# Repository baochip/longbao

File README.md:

# Longbao

Design files for the Longbao full pin breakout for the Baochip-1x.

The design is split into two halves, a small HDI board that uses laser-drilled vias to break out all the pins,
and a large conventional board that simply fans the break-out to castellated holes for easy prototyping.

The intention is that users who do not want to fab out an HDI board could re-use the HDI board in their design
as a "SOM".

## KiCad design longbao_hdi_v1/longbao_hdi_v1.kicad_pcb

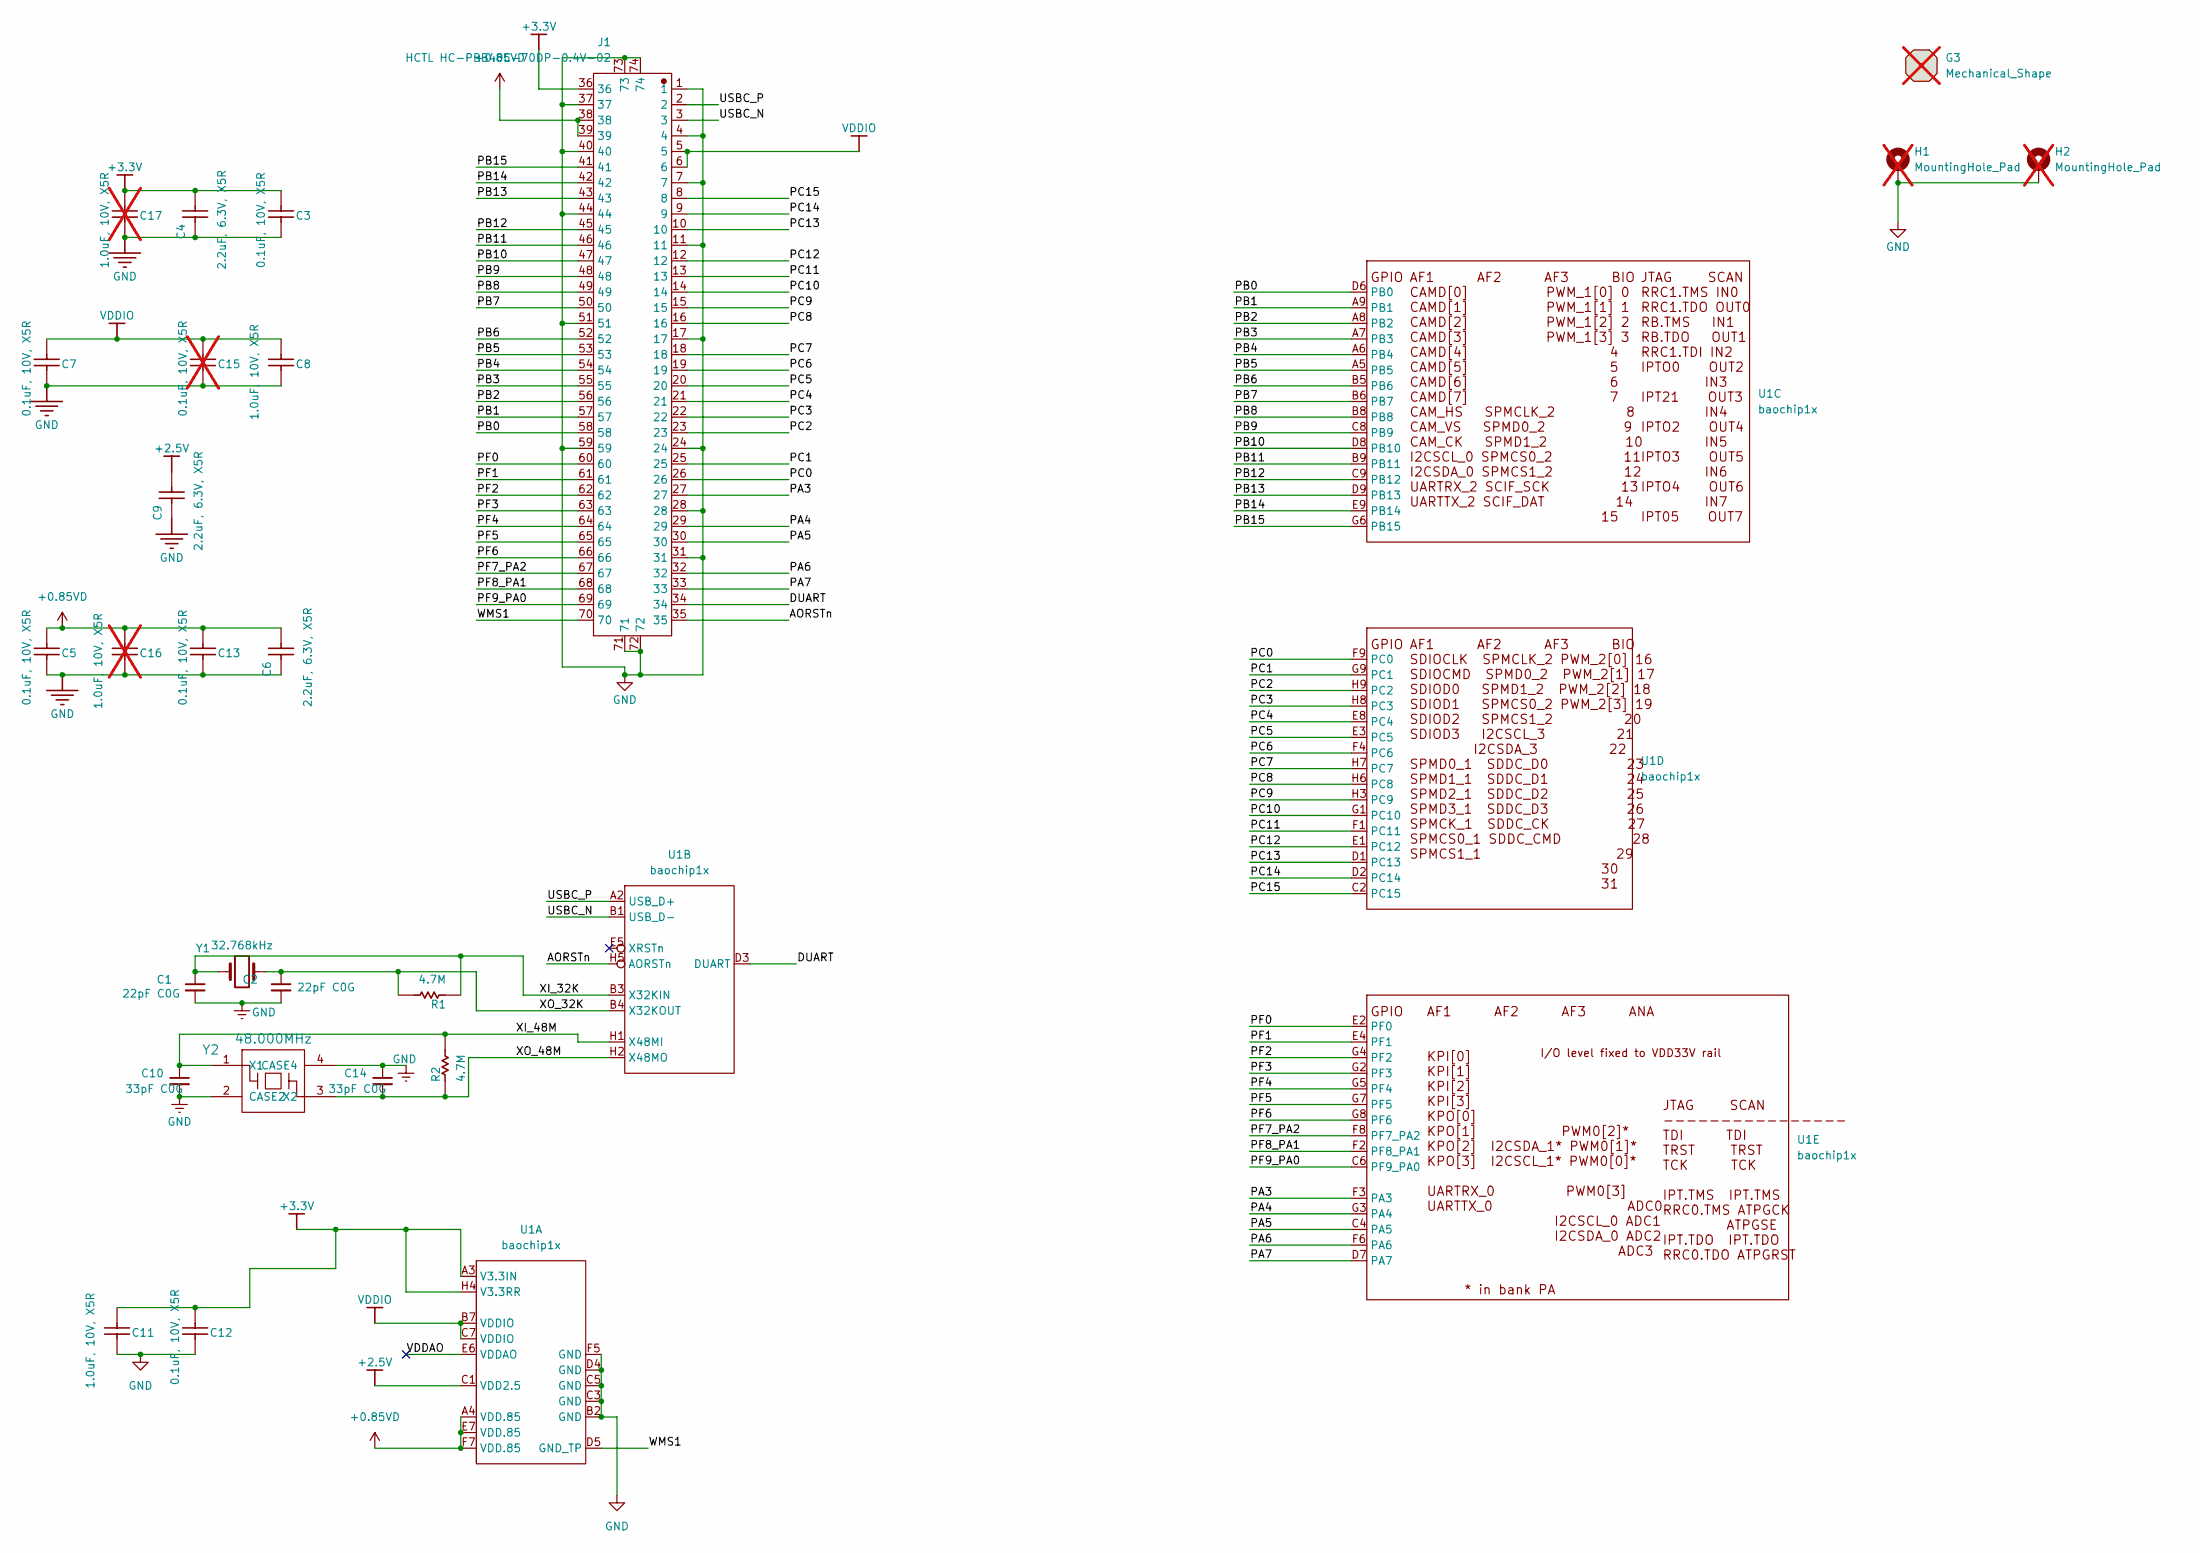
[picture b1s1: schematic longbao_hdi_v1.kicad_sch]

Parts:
C1, C2: 22pF C0G; C_0201_0603Metric; Rating C0G 50V 0201; MPN ANY; LCSC C57783
C3, C5, C7, C12, C13: 0.1uF, 10V, X5R; C_0201_0603Metric; MPN CL05B104KO5NNNC; LCSC C76934
C4, C6, C9: 2.2uF, 6.3V, X5R; C_0201_0603Metric; MPN GRM033R60J225ME47D; LCSC C76933
C8, C11: 1.0uF, 10V, X5R; C_0201_0603Metric; MPN CL05A105KA5NQNC; LCSC C76935
C10, C14: 33pF C0G; C_0201_0603Metric; Rating C0G 50V 0201; MPN ANY; LCSC C56903
C15: 0.1uF, 10V, X5R; C_0201_0603Metric; MPN CL05B104KO5NNNC; LCSC C76934; not fitted
C16, C17: 1.0uF, 10V, X5R; C_0201_0603Metric; MPN CL05A105KA5NQNC; LCSC C76935; not fitted
G3: Mechanical_Shape; CE-Logo_8.5x6mm_SilkScreen; not fitted
H1, H2: MountingHole_Pad; MountingHole_2.2mm_M2_DIN965_Pad; not fitted
J1: HCTL HC-PBB40C-70DP-0.4V-02; HC-PBB40C-70DP-0.4V-02; LCSC C19089236
R1, R2: 4.7M; R_0402_1005Metric; MPN ANY; LCSC C474132
U1: baochip1x; WLCSP-71_9x8_4.062x3.762mm; LCSC C9900312212
Y1: 32.768kHz; Crystal_SMD_TXC_9HT11-2Pin_2.0x1.2mm; LCSC C55208
Y2: 48.000MHz; Crystal_SMD_3225-4Pin_3.2x2.5mm; LCSC C2892060

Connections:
+0.85VD: C5.1, C6.2, C13.1, C16.1, J1.38, J1.39, U1.A4 (VDD.85), U1.E7 (VDD.85), U1.F7 (VDD.85)
+2.5V: C9.2, U1.C1 (VDD2.5)
+3.3V: C3.1, C4.2, C11.1, C12.1, C17.1, J1.36, U1.A3 (V3.3IN), U1.H4 (V3.3RR)
/AORSTn: J1.35, U1.H5 (AORSTn)
/DUART: J1.34, U1.D3 (DUART)
/PA3: J1.27, U1.F3 (PA3)
/PA4: J1.29, U1.G3 (PA4)
/PA5: J1.30, U1.C4 (PA5)
/PA6: J1.32, U1.F6 (PA6)
/PA7: J1.33, U1.D7 (PA7)
/PB0: J1.58, U1.D6 (PB0)
/PB1: J1.57, U1.A9 (PB1)
/PB2: J1.56, U1.A8 (PB2)
/PB3: J1.55, U1.A7 (PB3)
/PB4: J1.54, U1.A6 (PB4)
/PB5: J1.53, U1.A5 (PB5)
/PB6: J1.52, U1.B5 (PB6)
/PB7: J1.50, U1.B6 (PB7)
/PB8: J1.49, U1.B8
/PB9: J1.48, U1.C8 (PB9)
/PB10: J1.47, U1.D8 (PB10)
/PB11: J1.46, U1.B9 (PB11)
/PB12: J1.45, U1.C9 (PB12)
/PB13: J1.43, U1.D9 (PB13)
/PB14: J1.42, U1.E9 (PB14)
/PB15: J1.41, U1.G6 (PB15)
/PC0: J1.26, U1.F9 (PC0)
/PC1: J1.25, U1.G9 (PC1)
/PC2: J1.23, U1.H9 (PC2)
/PC3: J1.22, U1.H8 (PC3)
/PC4: J1.21, U1.E8 (PC4)
/PC5: J1.20, U1.E3 (PC5)
/PC6: J1.19, U1.F4 (PC6)
/PC7: J1.18, U1.H7 (PC7)
/PC8: J1.16, U1.H6 (PC8)
/PC9: J1.15, U1.H3 (PC9)
/PC10: J1.14, U1.G1 (PC10)
/PC11: J1.13, U1.F1 (PC11)
/PC12: J1.12, U1.E1 (PC12)
/PC13: J1.10, U1.D1 (PC13)
/PC14: J1.9, U1.D2 (PC14)
/PC15: J1.8, U1.C2 (PC15)
/PF0: J1.60, U1.E2 (PF0)
/PF1: J1.61, U1.E4 (PF1)
/PF2: J1.62, U1.G4 (PF2)
/PF3: J1.63, U1.G2 (PF3)
/PF4: J1.64, U1.G5 (PF4)
/PF5: J1.65, U1.G7 (PF5)
/PF6: J1.66, U1.G8 (PF6)
/PF7_PA2: J1.67, U1.F8 (PF7_PA2)
/PF8_PA1: J1.68, U1.F2 (PF8_PA1)
/PF9_PA0: J1.69, U1.C6 (PF9_PA0)
/USBC_N: J1.3, U1.B1 (USB_D-)
/USBC_P: J1.2, U1.A2 (USB_D+)
/VDDAO: U1.E6 (VDDAO)
/WMS1: J1.70, U1.D5 (GND_TP)
/XI_32K: C1.1, R1.1, U1.B3 (X32KIN), Y1.1
/XI_48M: C10.1, R2.2, U1.H1 (X48MI), Y2.1 (X1)
/XO_32K: C2.1, R1.2, U1.B4 (X32KOUT), Y1.2
/XO_48M: C14.2, R2.1, U1.H2 (X48MO), Y2.3 (X2)
GND: C1.2, C2.2, C3.2, C4.1, C5.2, C6.1, C7.2, C8.2, C9.1, C10.2, C11.2, C12.2, C13.2, C14.1, C15.2, C16.2, C17.2, H1.1 (1_1), H2.1 (1_1), J1.1, J1.4, J1.7, J1.11, J1.17, J1.24, J1.28, J1.31, J1.37, J1.40, J1.44, J1.51, J1.59, J1.71, J1.72, J1.73, J1.74, U1.B2 (GND), U1.C3 (GND), U1.C5 (GND), U1.D4 (GND), U1.F5 (GND), Y2.2 (CASE2), Y2.4 (CASE4)
VDDIO: C7.1, C8.1, C15.1, J1.5, J1.6, U1.B7 (VDDIO), U1.C7 (VDDIO)

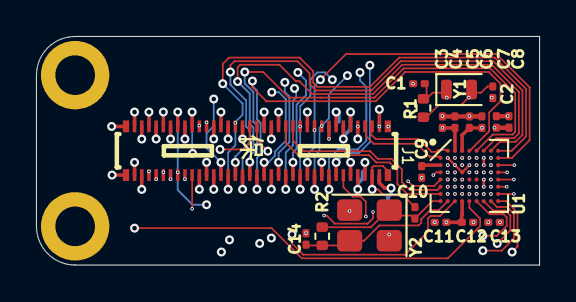
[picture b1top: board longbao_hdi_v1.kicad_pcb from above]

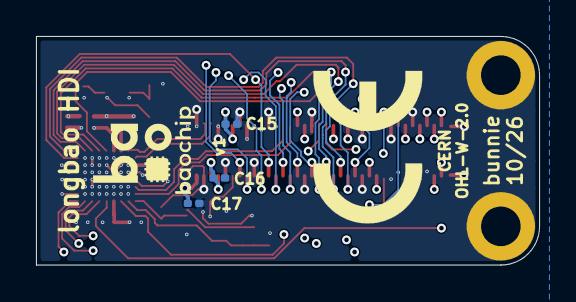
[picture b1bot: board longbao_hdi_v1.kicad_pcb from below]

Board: 6 copper layers, 28.0 x 12.7 mm, 28 parts (5 on the bottom side), 61 nets.

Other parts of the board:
G1, G2: LOGO

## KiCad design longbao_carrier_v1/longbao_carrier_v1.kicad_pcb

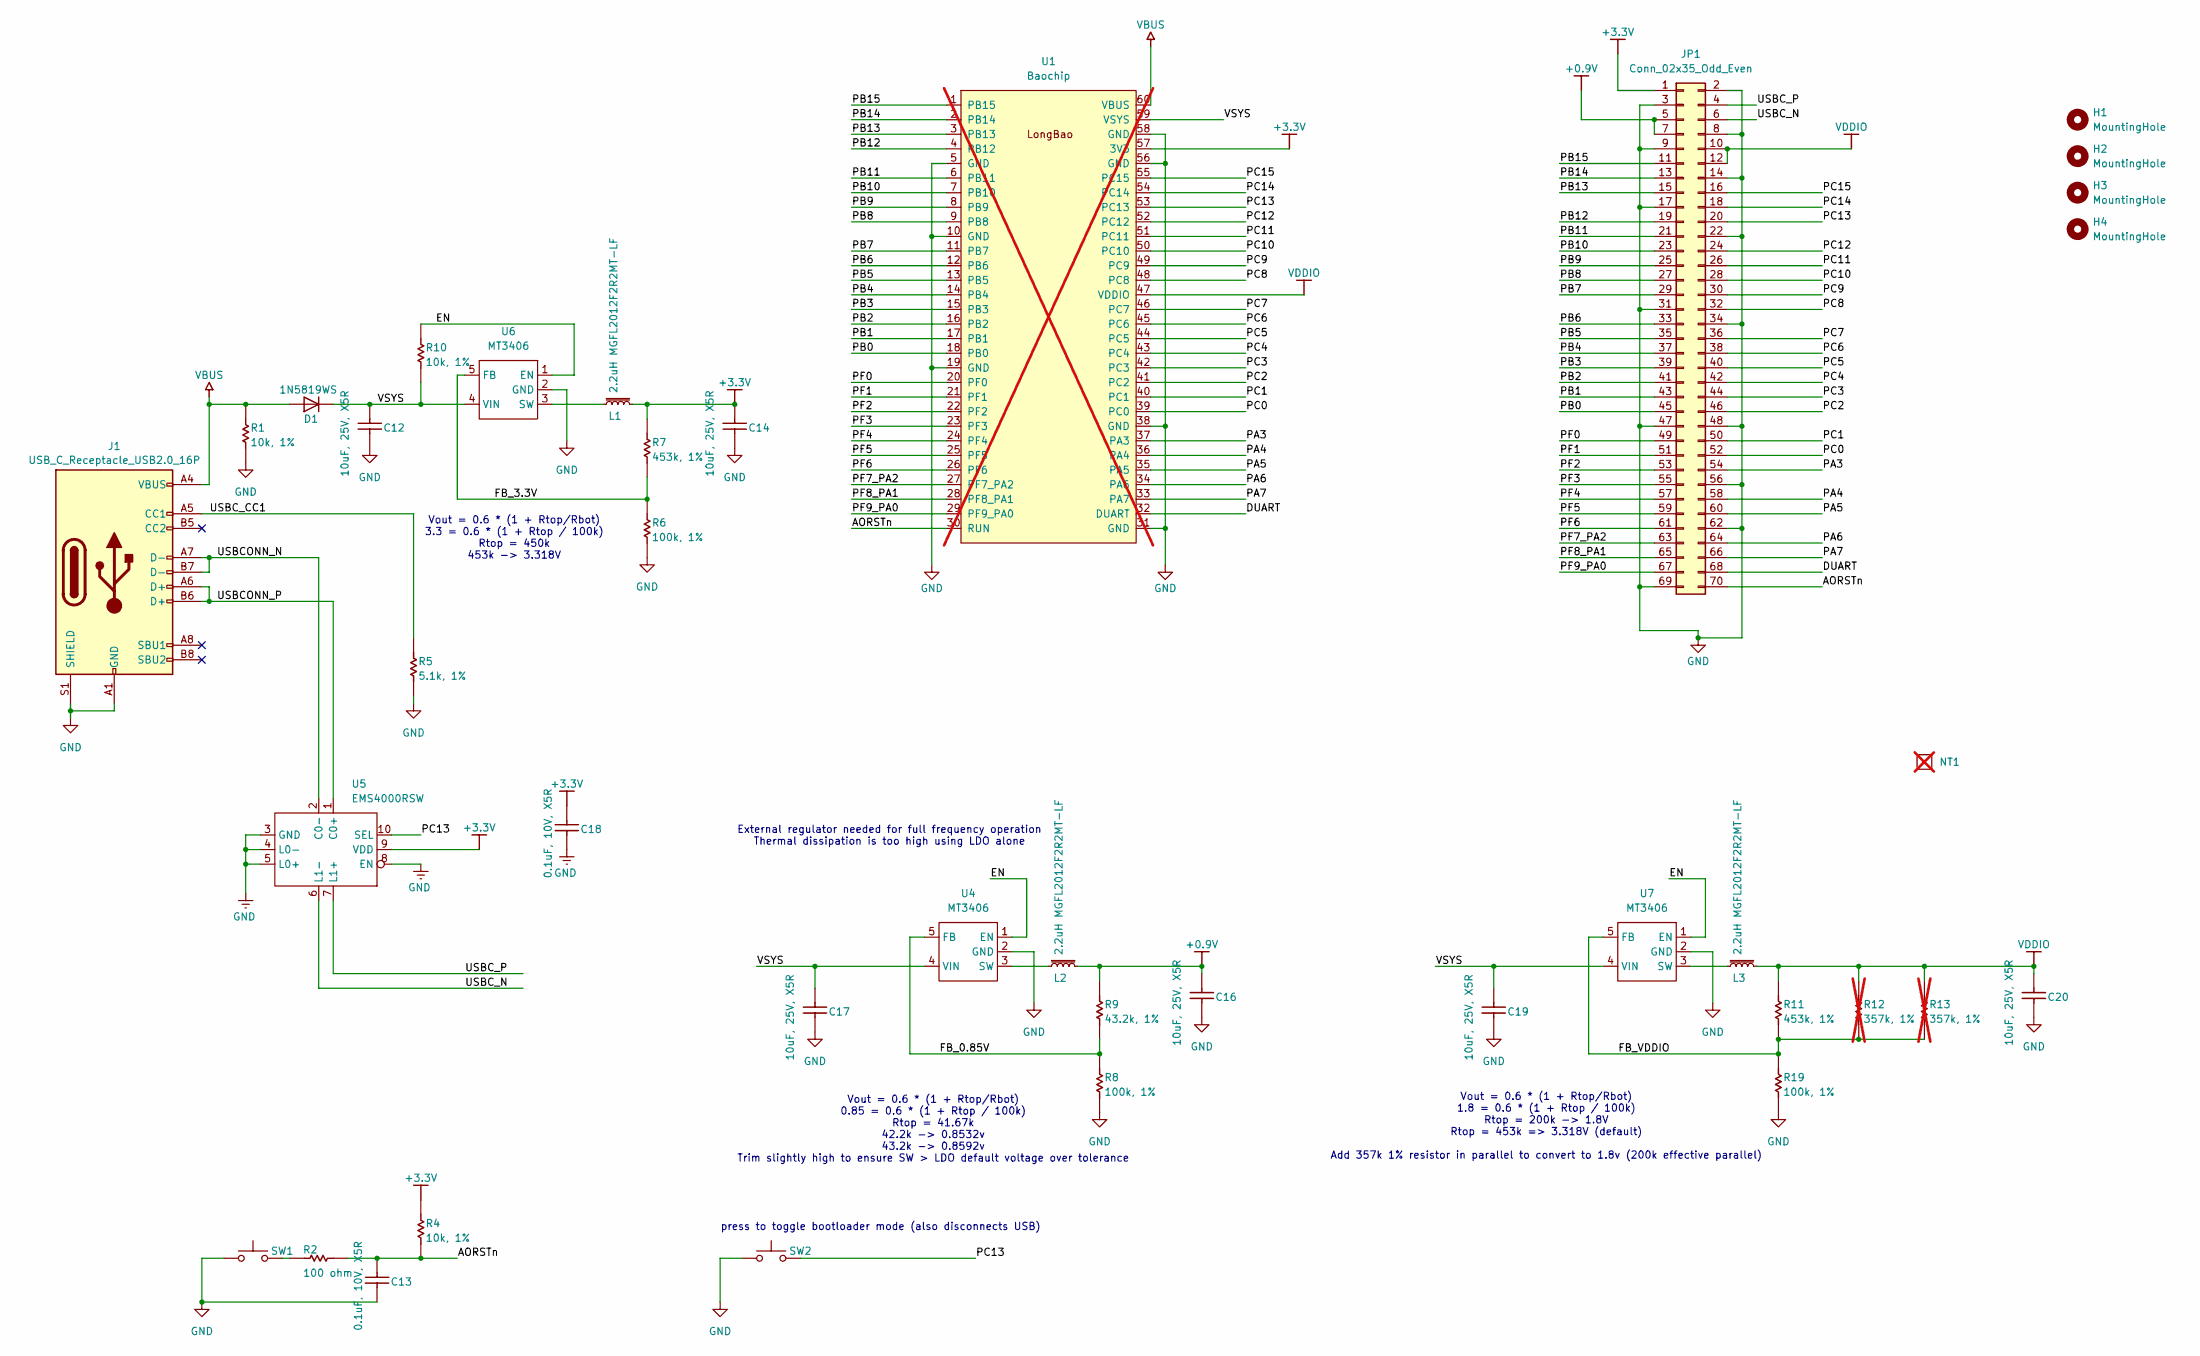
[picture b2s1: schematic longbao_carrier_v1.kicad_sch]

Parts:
C12, C14, C16, C17, C19, C20: 10uF, 25V, X5R; C_0603_1608Metric; MPN CL10A106MA8NRNC; LCSC C96446
C13, C18: 0.1uF, 10V, X5R; C_0201_0603Metric; MPN CL05B104KO5NNNC; LCSC C76934
D1: 1N5819WS; D_SOD-323; MPN SD103AWS; LCSC C191023
H1, H2, H3, H4: MountingHole; MountingHole_2.2mm_M2_DIN965
J1: USB_C_Receptacle_USB2.0_16P; USB_C_Receptacle_HRO_TYPE-C-31-M-12; LCSC C165948
JP1: Conn_02x35_Odd_Even; HC-PBB40C-70DS-0.4V-2.5-02; LCSC C19089322
L1, L2, L3: 2.2uH MGFL2012F2R2MT-LF; L_0805_2012Metric; LCSC C281115
NT1: CE-Logo_8.5x6mm_SilkScreen; not fitted
R1, R4, R10: 10k, 1%; R_0201_0603Metric; MPN ANY; LCSC C106225
R2: 100 ohm; R_0402_1005Metric; MPN ANY; LCSC C106232
R5: 5.1k, 1%; R_0402_1005Metric; MPN ANY; LCSC C25905
R6, R8, R19: 100k, 1%; R_0201_0603Metric; MPN ANY; LCSC C106224
R7, R11: 453k, 1%; R_0201_0603Metric; MPN ANY; LCSC C423509
R9: 43.2k, 1%; R_0201_0603Metric; MPN ANY; LCSC C158519
R12: 357k, 1%; R_1206_3216Metric; MPN ANY; LCSC DNP; not fitted
R13: 357k, 1%; R_Axial_DIN0207_L6.3mm_D2.5mm_P7.62mm_Horizontal; MPN ANY; LCSC DNP; not fitted
SW1, SW2: SW_Push; TS3425BA; LCSC C2681476
U1: Baochip; Longbao_Vendor_Substrate; not fitted
U4, U6, U7: MT3406; SOT-23-5; LCSC C22462728
U5: EMS4000RSW; QFN-10_1.4x1.8_Pitch0.4mm; LCSC C49186227

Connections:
+0.9V: C16.1, JP1.5, JP1.7, L2.2, R9.1
+3.3V: C14.1, C18.1, JP1.1, L1.2, R4.1, R7.1, U1.57 (3V3), U5.9 (VDD)
/AORSTn: C13.1, JP1.70, R2.2, R4.2, U1.30 (RUN)
/DUART: JP1.68, U1.32 (DUART)
/EN: R10.1, U4.1 (EN), U6.1 (EN), U7.1 (EN)
/FB_0.85V: R8.1, R9.2, U4.5 (FB)
/FB_3.3V: R6.1, R7.2, U6.5 (FB)
/FB_VDDIO: R11.2, R12.2, R13.2, R19.1, U7.5 (FB)
/PA3: JP1.54, U1.37 (PA3)
/PA4: JP1.58, U1.36 (PA4)
/PA5: JP1.60, U1.35 (PA5)
/PA6: JP1.64, U1.34 (PA6)
/PA7: JP1.66, U1.33 (PA7)
/PB0: JP1.45, U1.18 (PB0)
/PB1: JP1.43, U1.17 (PB1)
/PB2: JP1.41, U1.16 (PB2)
/PB3: JP1.39, U1.15 (PB3)
/PB4: JP1.37, U1.14 (PB4)
/PB5: JP1.35, U1.13 (PB5)
/PB6: JP1.33, U1.12 (PB6)
/PB7: JP1.29, U1.11 (PB7)
/PB8: JP1.27, U1.9 (PB8)
/PB9: JP1.25, U1.8 (PB9)
/PB10: JP1.23, U1.7 (PB10)
/PB11: JP1.21, U1.6 (PB11)
/PB12: JP1.19, U1.4 (PB12)
/PB13: JP1.15, U1.3 (PB13)
/PB14: JP1.13, U1.2 (PB14)
/PB15: JP1.11, U1.1 (PB15)
/PC0: JP1.52, U1.39 (PC0)
/PC1: JP1.50, U1.40 (PC1)
/PC2: JP1.46, U1.41 (PC2)
/PC3: JP1.44, U1.42 (PC3)
/PC4: JP1.42, U1.43 (PC4)
/PC5: JP1.40, U1.44 (PC5)
/PC6: JP1.38, U1.45 (PC6)
/PC7: JP1.36, U1.46 (PC7)
/PC8: JP1.32, U1.48 (PC8)
/PC9: JP1.30, U1.49 (PC9)
/PC10: JP1.28, U1.50 (PC10)
/PC11: JP1.26, U1.51 (PC11)
/PC12: JP1.24, U1.52 (PC12)
/PC13: JP1.20, SW2.2, U1.53 (PC13), U5.10 (SEL)
/PC14: JP1.18, U1.54 (PC14)
/PC15: JP1.16, U1.55 (PC15)
/PF0: JP1.49, U1.20 (PF0)
/PF1: JP1.51, U1.21 (PF1)
/PF2: JP1.53, U1.22 (PF2)
/PF3: JP1.55, U1.23 (PF3)
/PF4: JP1.57, U1.24 (PF4)
/PF5: JP1.59, U1.25 (PF5)
/PF6: JP1.61, U1.26 (PF6)
/PF7_PA2: JP1.63, U1.27 (PF7_PA2)
/PF8_PA1: JP1.65, U1.28 (PF8_PA1)
/PF9_PA0: JP1.67, U1.29 (PF9_PA0)
/USBCONN_N: J1.A7 (D-), J1.B7 (D-), U5.2 (C0-)
/USBCONN_P: J1.A6 (D+), J1.B6 (D+), U5.1 (C0+)
/USBC_CC1: J1.A5 (CC1), R5.2
/USBC_N: JP1.6, U5.6 (L1-)
/USBC_P: JP1.4, U5.7 (L1+)
/VSYS: C12.1, C17.1, C19.1, D1.1 (K), R10.2, U1.59 (VSYS), U4.4 (VIN), U6.4 (VIN), U7.4 (VIN)
GND: C12.2, C13.2, C14.2, C16.2, C17.2, C18.2, C19.2, C20.2, J1.A1 (GND), J1.A12 (GND), J1.B1 (GND), J1.B12 (GND), J1.S1 (SHIELD), JP1.2, JP1.3, JP1.8, JP1.9, JP1.14, JP1.17, JP1.22, JP1.31, JP1.34, JP1.47, JP1.48, JP1.56, JP1.62, JP1.69, R1.2, R5.1, R6.2, R8.2, R19.2, SW1.1, SW2.1, U1.5 (GND), U1.10 (GND), U1.19 (GND), U1.31 (GND), U1.38 (GND), U1.56 (GND), U1.58 (GND), U4.2 (GND), U5.3 (GND), U5.4 (L0-), U5.5 (L0+), U5.8 (EN), U6.2 (GND), U7.2 (GND)
unnamed: R2.1, SW1.2
unnamed: L2.1, U4.3 (SW)
unnamed: L1.1, U6.3 (SW)
unnamed: L3.1, U7.3 (SW)
VBUS: D1.2 (A), J1.A4 (VBUS), J1.A9 (VBUS), J1.B4 (VBUS), J1.B9 (VBUS), R1.1, U1.60 (VBUS)
VDDIO: C20.1, JP1.10, JP1.12, L3.2, R11.1, R12.1, R13.1, U1.47 (VDDIO)

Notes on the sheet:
Vout = 0.6 * (1 + Rtop/Rbot) 3.3 = 0.6 * (1 + Rtop / 100k) Rtop = 450k 453k -> 3.318V
Vout = 0.6 * (1 + Rtop/Rbot) 1.8 = 0.6 * (1 + Rtop / 100k) Rtop = 200k -> 1.8V Rtop = 453k => 3.318V (default) Add 357k 1% resistor in parallel to convert to 1.8v (200k effective parallel)
External regulator needed for full frequency operation Thermal dissipation is too high using LDO alone
press to toggle bootloader mode (also disconnects USB)
Vout = 0.6 * (1 + Rtop/Rbot) 0.85 = 0.6 * (1 + Rtop / 100k) Rtop = 41.67k 42.2k -> 0.8532v 43.2k -> 0.8592v Trim slightly high to ensure SW > LDO default voltage over tolerance

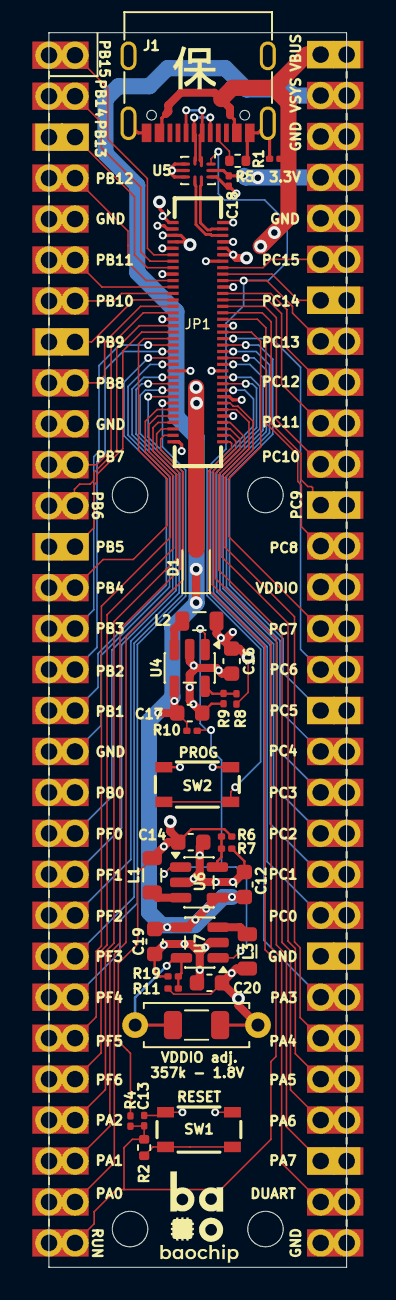
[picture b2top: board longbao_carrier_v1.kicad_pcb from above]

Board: 4 copper layers, 18.5 x 76.6 mm, 39 parts (1 on the bottom side), 68 nets.
